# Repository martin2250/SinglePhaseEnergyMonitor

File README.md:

# SinglePhaseEnergyMonitor

an adapter to plug between a device and an outlet, to monitor electricity usage and provide data to influxdb

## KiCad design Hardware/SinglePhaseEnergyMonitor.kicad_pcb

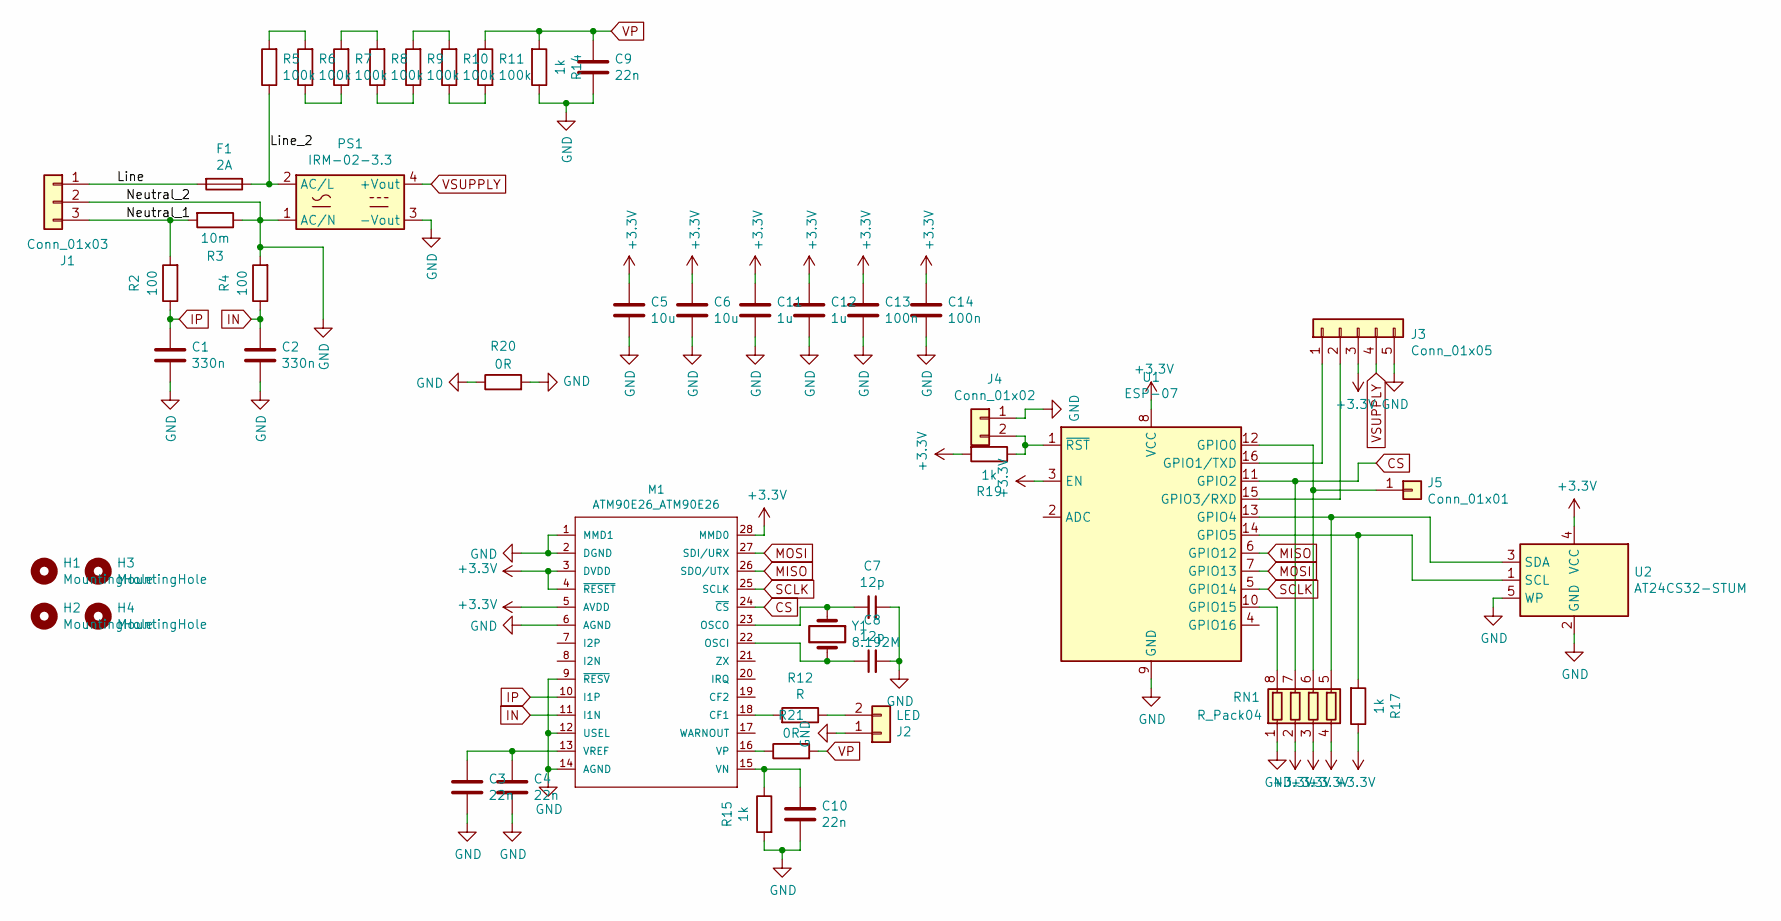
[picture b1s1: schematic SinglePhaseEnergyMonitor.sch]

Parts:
C1, C2: 330n; C_1206_3216Metric
C3, C4, C9, C10: 22n; C_0805_2012Metric
C5, C6: 10u; C_1206_3216Metric
C7, C8: 12p; C_0805_2012Metric
C11, C12: 1u; C_0805_2012Metric
C13, C14: 100n; C_0805_2012Metric
F1: 2A; Fuseholder_Cylinder-5x20mm_Stelvio-Kontek_PTF78_Horizontal_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
H1, H2, H3, H4: MountingHole; MountingHole_3mm
J1: Conn_01x03; TerminalBlock_RND_205-00046_1x03_P5.00mm_Horizontal
J2: LED; PinHeader_1x02_P2.54mm_Vertical
J3: Conn_01x05; PinHeader_1x05_P2.54mm_Vertical
J4: Conn_01x02; PinHeader_1x02_P2.54mm_Vertical
J5: Conn_01x01; Pin_D0.9mm_L10.0mm_W2.4mm_FlatFork
M1: ATM90E26_ATM90E26; SSOP-28_5.3x10.2mm_P0.65mm
PS1: IRM-02-3.3; Converter_ACDC_MeanWell_IRM-02-xx_THT
R2, R4: 100; R_1206_3216Metric
R3: 10m; R_Box_L14.0mm_W5.0mm_P9.00mm
R5, R6, R7, R8, R9, R10, R11: 100k; R_1206_3216Metric
R12: R; R_1206_3216Metric
R14, R15, R17, R19: 1k; R_0805_2012Metric
R20, R21: 0R; R_1206_3216Metric
RN1: R_Pack04; R_Array_Convex_4x0603
U1: ESP-07
U2: AT24CS32-STUM; SOT-23-5
Y1: 8.192M; Crystal_SMD_HC49-SD

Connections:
+3V3: C5.2, C6.2, C11.2, C12.2, C13.2, C14.2, J3.3, M1.3 (DVDD), M1.4 (~RESET), M1.5 (AVDD), M1.28 (MMD0), R17.1, R19.2, RN1.2 (R2.1), RN1.3 (R3.1), RN1.4 (R4.1), U1.3 (EN), U1.8 (VCC), U2.4 (VCC)
/Line: F1.2, J1.1
/Line_2: F1.1, PS1.2 (AC/L), R5.1
/Neutral_1: J1.3, R2.2, R3.2
CS: M1.24 (~CS), RN1.7 (R2.2), U1.11 (GPIO2)
GND: C1.2, C2.1, C3.1, C4.1, C5.1, C6.1, C7.1, C8.2, C9.1, C10.1, C11.1, C12.1, C13.1, C14.1, J1.2, J2.1, J3.5, J4.1, M1.1 (MMD1), M1.2 (DGND), M1.6 (AGND), M1.9 (~RESV), M1.12 (USEL), M1.14 (AGND), PS1.1 (AC/N), PS1.3 (-Vout), R3.1, R4.2, R14.1, R15.2, R20.1, R20.2, RN1.1 (R1.1), U1.9 (GND), U2.2 (GND), U2.5 (WP)
IN: C2.2, M1.11 (I1N), R4.1
IP: C1.1, M1.10 (I1P), R2.1
MISO: M1.26 (SDO/UTX), U1.6 (GPIO12)
MOSI: M1.27 (SDI/URX), U1.7 (GPIO13)
unnamed: C3.2, C4.2, M1.13 (VREF)
unnamed: C7.2, M1.23 (OSCO), Y1.1
unnamed: C8.1, M1.22 (OSCI), Y1.2
unnamed: C10.2, M1.15 (VN), R15.1
unnamed: J2.2, R12.1
unnamed: J3.1, U1.16 (GPIO1/TXD)
unnamed: J3.2, U1.15 (GPIO3/RXD)
unnamed: J4.2, R19.1, U1.1 (~RST)
unnamed: J5.1, RN1.6 (R3.2), U1.12 (GPIO0)
unnamed: M1.16 (VP), R21.1
unnamed: M1.18 (CF1), R12.2
unnamed: R5.2, R6.2
unnamed: R6.1, R7.1
unnamed: R7.2, R8.2
unnamed: R8.1, R9.1
unnamed: R10.1, R11.2
unnamed: R9.2, R10.2
unnamed: R17.2, U1.14 (GPIO5), U2.1 (SCL)
unnamed: RN1.5 (R4.2), U1.13 (GPIO4), U2.3 (SDA)
unnamed: RN1.8 (R1.2), U1.10 (GPIO15)
SCLK: M1.25 (SCLK), U1.5 (GPIO14)
VP: C9.2, R11.1, R14.2, R21.2
VSUPPLY: J3.4, PS1.4 (+Vout)

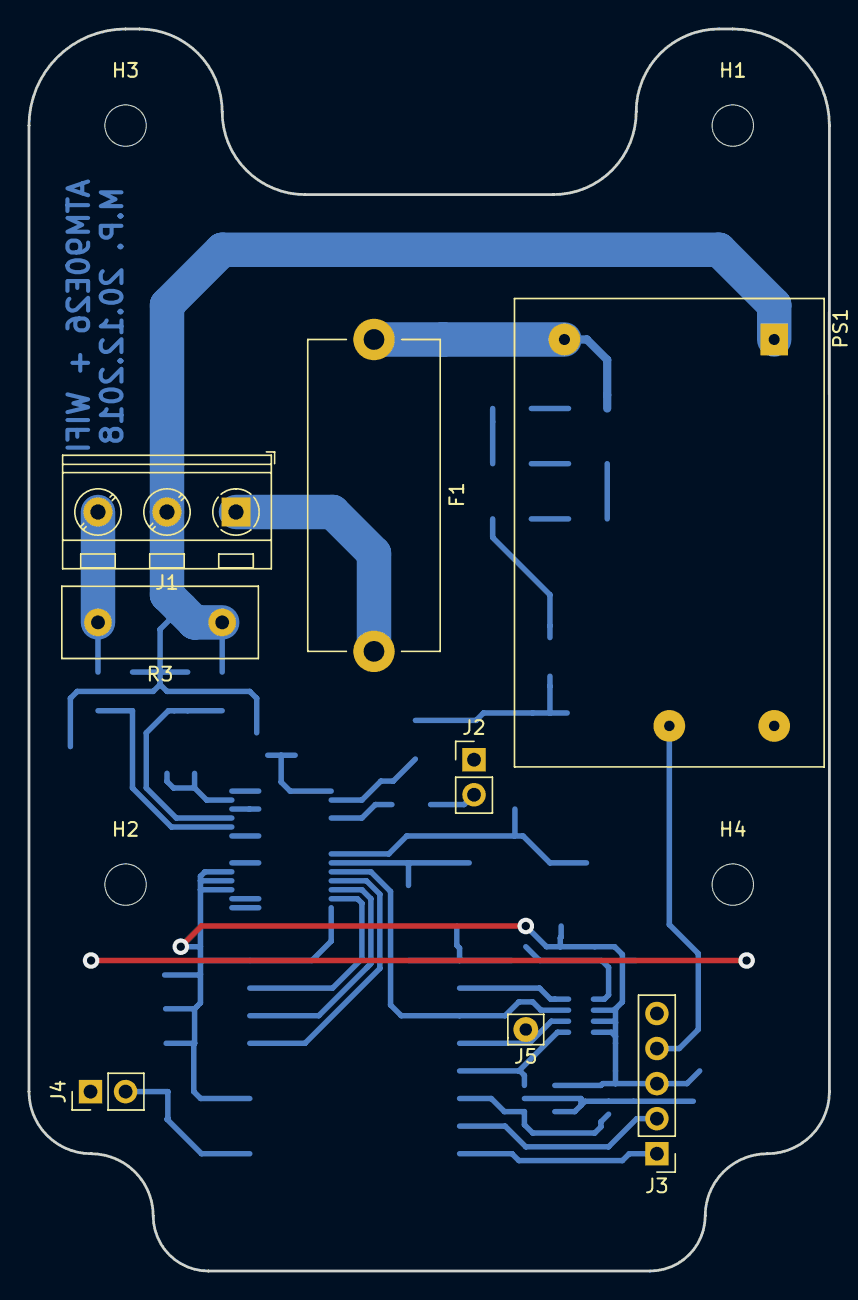
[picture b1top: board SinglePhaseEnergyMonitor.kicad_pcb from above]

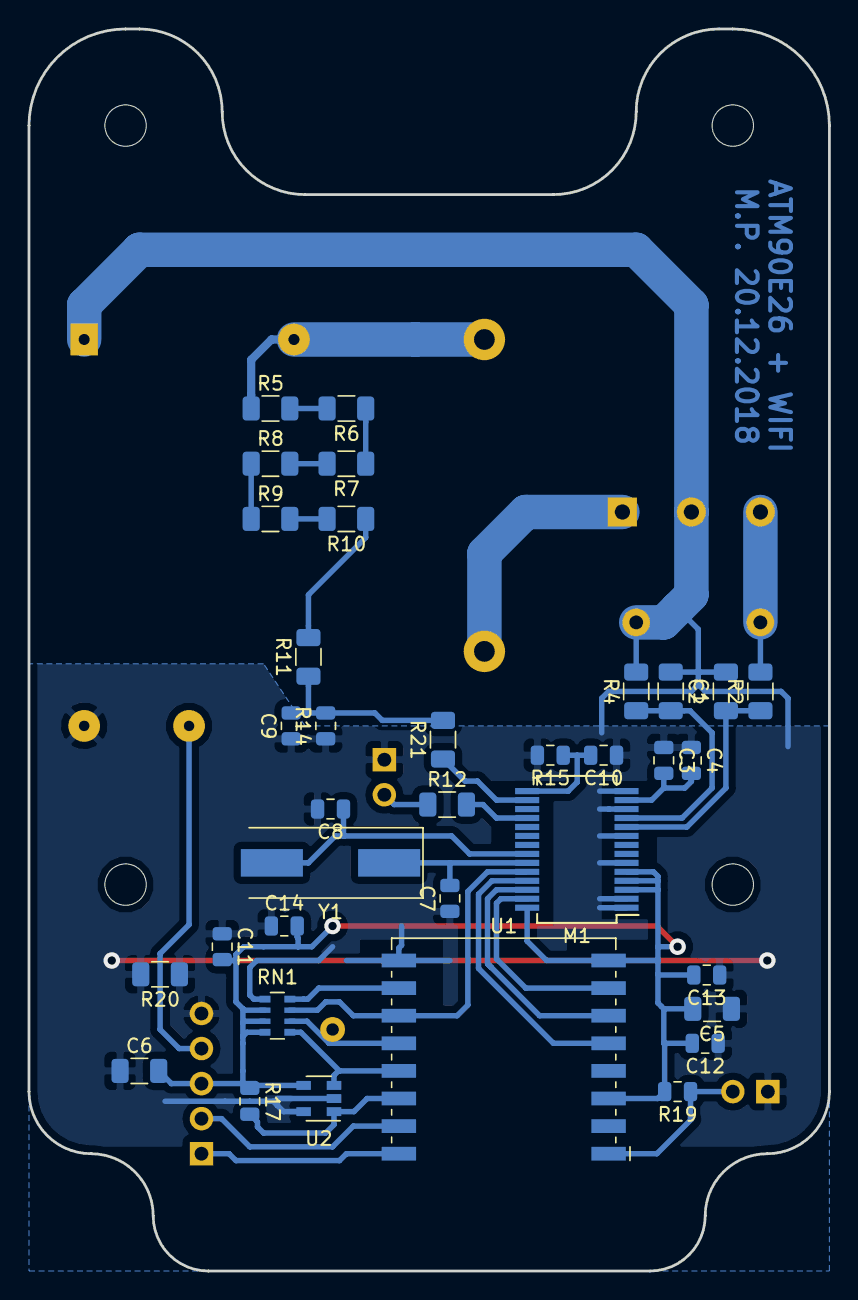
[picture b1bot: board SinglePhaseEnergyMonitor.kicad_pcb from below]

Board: 2 copper layers, 58.0 x 90.0 mm, 47 parts (35 on the bottom side), 33 nets.

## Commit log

2018-12-25 Create LICENSE
2018-12-25 add loop duration tracker
2018-12-25 improve layout
2018-12-28 add more decimal places to metrics
2019-02-02 made AP not always on
2019-02-06 made AP toggle with RTC mem
2019-02-06 fix pcb
2019-02-07 add cal data
2019-02-12 add metric pusher
2019-02-19 major rework to use settingsmanager library
2019-02-19 update to new metric format
2019-02-20 made settings push client persistent
2019-02-21 add setAutoReconnect
